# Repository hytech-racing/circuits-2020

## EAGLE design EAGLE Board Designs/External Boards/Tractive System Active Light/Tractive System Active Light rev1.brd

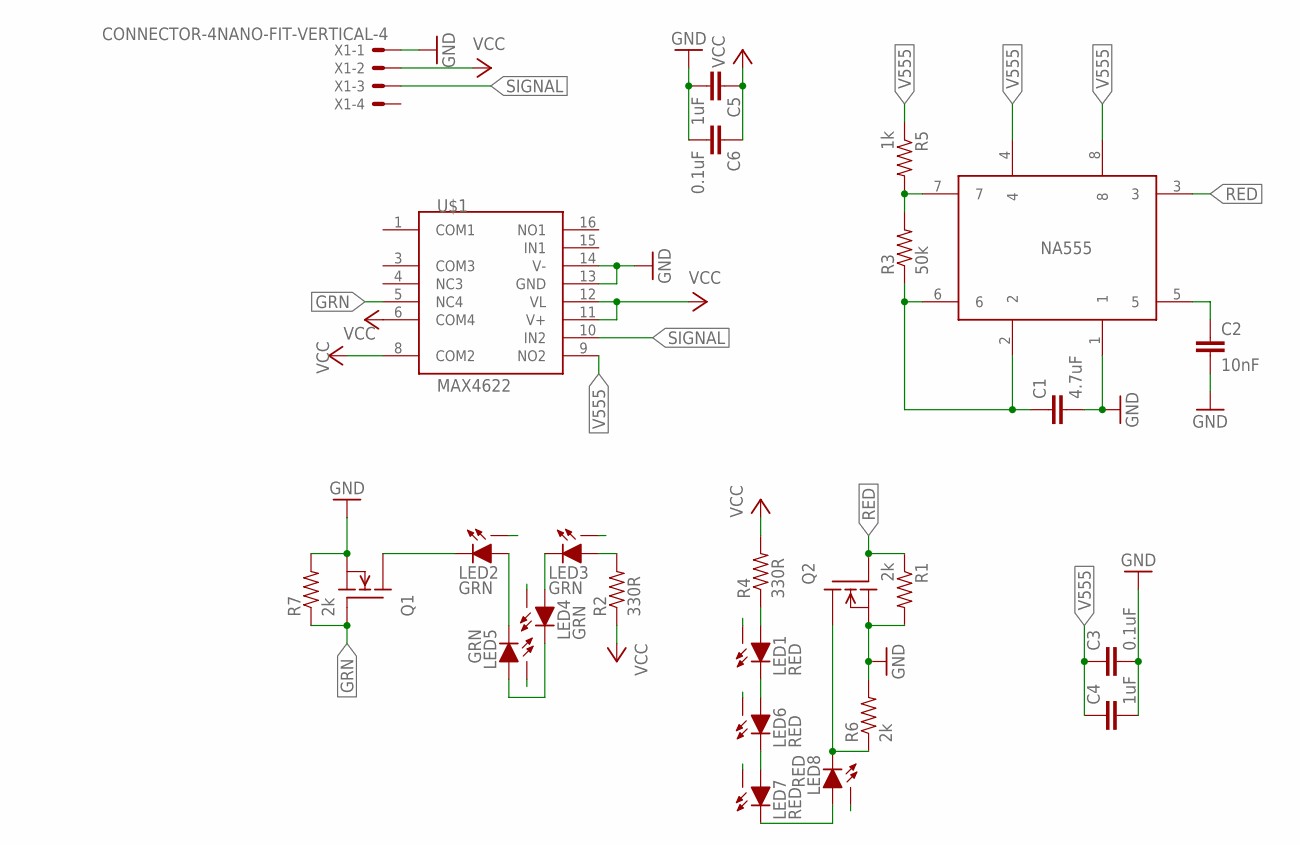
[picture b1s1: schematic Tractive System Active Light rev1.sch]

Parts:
C1: 4.7uF; 0603-CAP
C2: 10nF; 0603-CAP
C3, C6: 0.1uF; 0603-CAP
C4, C5: 1uF; 0603-CAP
LED1, LED6, LED7, LED8: RED; XP-E2
LED2, LED3, LED4, LED5: GRN; XP-E2
NA555: NA555SO-8; SOIC-08
Q1, Q2: DMG3406LSOT; SOT23
R1, R6, R7: 2k; 0603-RES
R2, R4: 330R; 0603-RES
R3: 50k; 0603-RES
R5: 1k; 0603-RES
U$1: MAX4622; SO16
X1: CONNECTOR-4NANO-FIT-VERTICAL-4; NANO-FIT_VERTICAL-4

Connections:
GND: C1.2, C2.2, C3.2, C4.2, C5.2, C6.2, NA555.1, Q1.2 (S), Q2.2 (S), R1.2, R6.2, R7.2, U$1.13 (GND), U$1.14 (V-), X1.P$1
GRN: Q1.1 (G), R7.1, U$1.5 (NC4)
LED1_THERM: LED1.X
LED2_THERM: LED2.X
LED3_THERM: LED3.X
LED4_THERM: LED4.X
LED5_THERM: LED5.X
LED6_THERM: LED6.X
LED7_THERM: LED7.X
LED8_THERM: LED8.X
unnamed: LED4.C, LED5.A
unnamed: LED2.C, Q1.3 (D)
unnamed: LED3.C, LED4.A
unnamed: LED3.A, R2.2
unnamed: C1.1, NA555.2, NA555.6, R3.1
unnamed: NA555.7, R3.2, R5.2
unnamed: LED8.C, Q2.3 (D), R6.1
unnamed: LED1.A, R4.1
unnamed: C2.1, NA555.5
unnamed: LED2.A, LED5.C
unnamed: LED1.C, LED6.A
unnamed: LED6.C, LED7.A
unnamed: LED7.C, LED8.A
RED: NA555.3, Q2.1 (G), R1.1
SIGNAL: U$1.10 (IN2), X1.P$3
V555: C3.1, C4.1, NA555.4, NA555.8, R5.1, U$1.9 (NO2)
VCC: C5.1, C6.1, R2.1, R4.2, U$1.6 (COM4), U$1.8 (COM2), U$1.11 (V+), U$1.12 (VL), X1.P$2

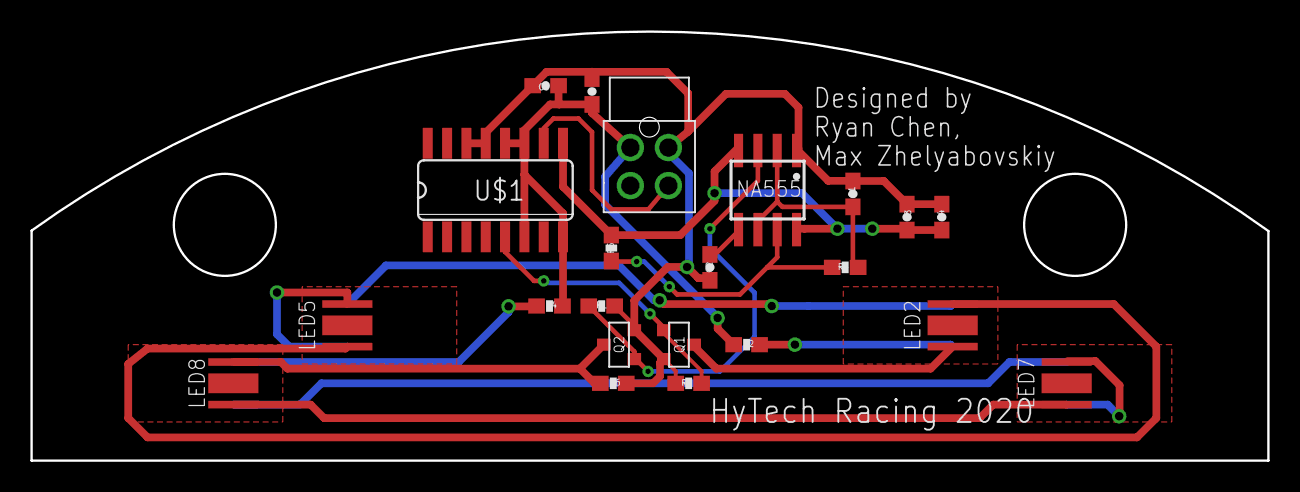
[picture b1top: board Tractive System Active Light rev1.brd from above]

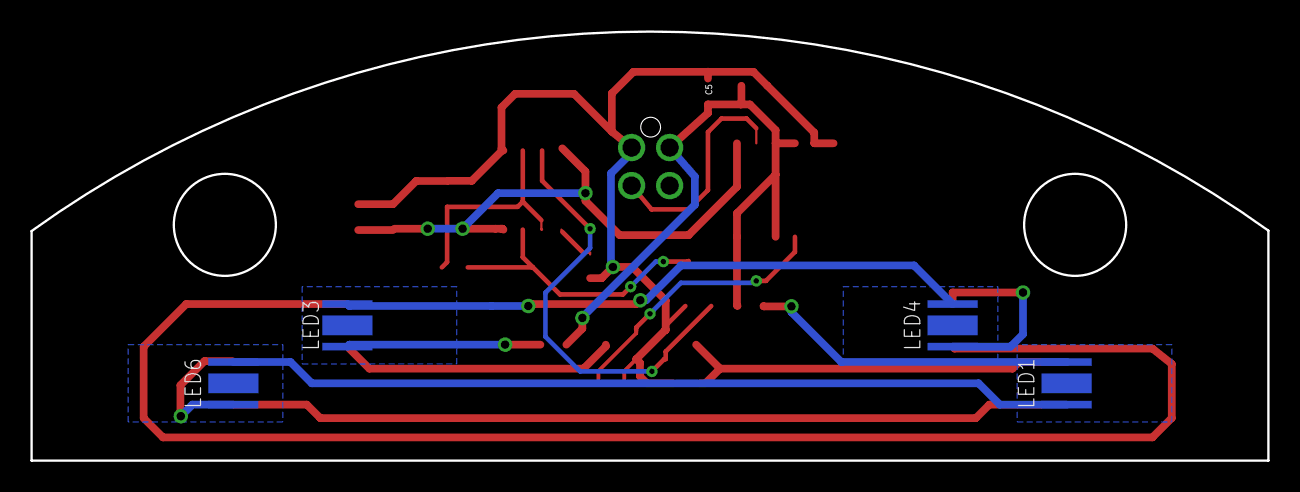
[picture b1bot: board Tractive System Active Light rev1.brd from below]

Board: 2 copper layers, 81.3 x 28.2 mm, 26 parts (4 on the bottom side), 19 nets.

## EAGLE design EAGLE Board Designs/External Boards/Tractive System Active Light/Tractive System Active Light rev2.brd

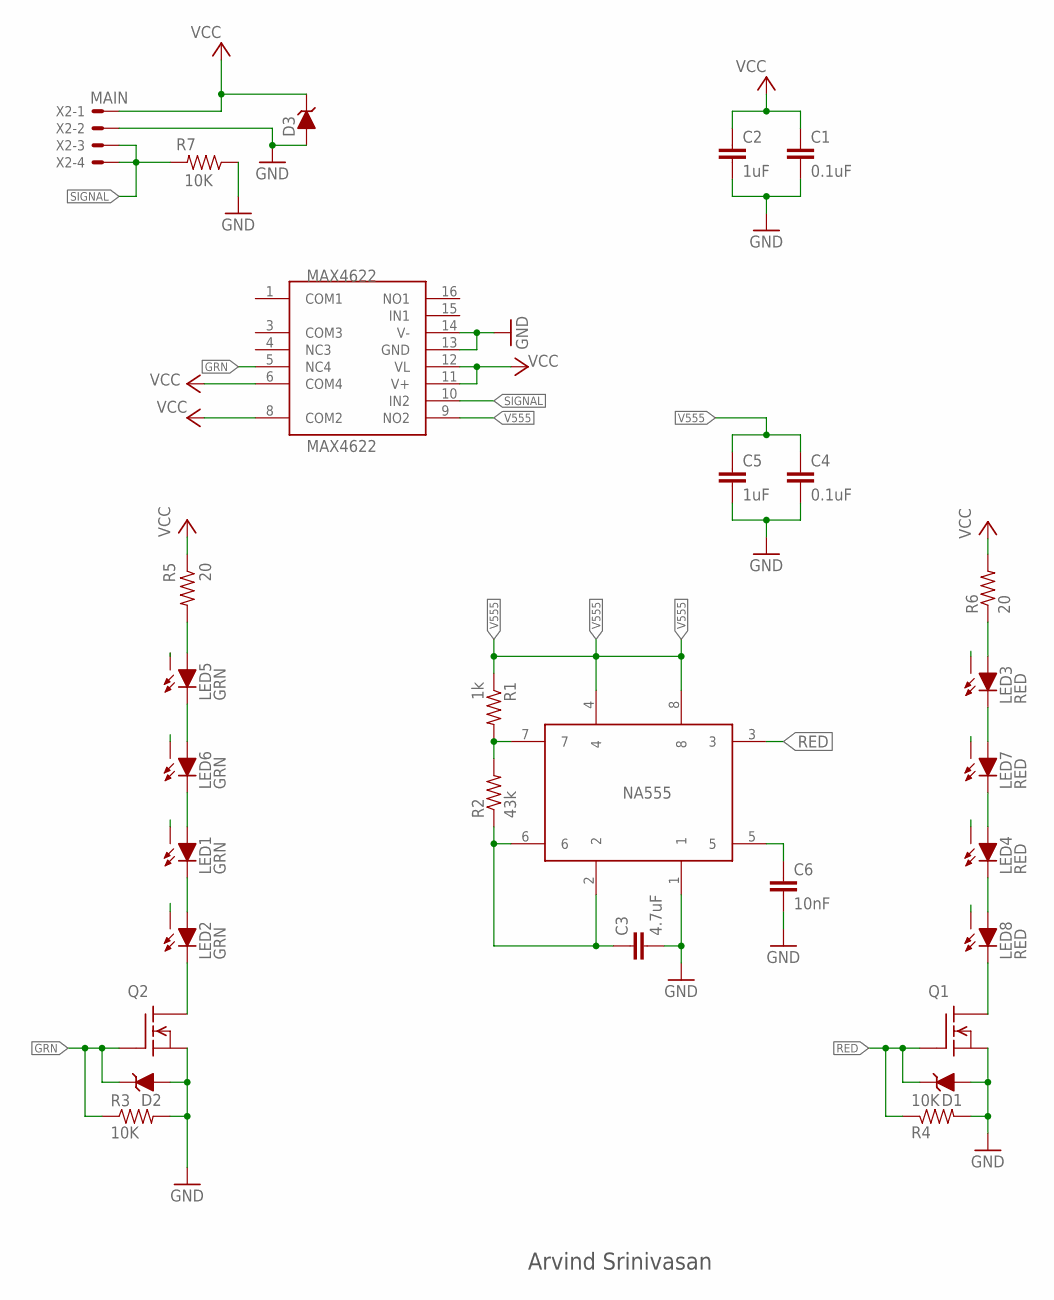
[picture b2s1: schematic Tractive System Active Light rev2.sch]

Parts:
C1, C4: 0.1uF; 0603-CAP; TOLERANCE 5%; VOLTAGE 25V
C2, C5: 1uF; 0603-CAP; TOLERANCE 5%; VOLTAGE 25V
C3: 4.7uF; 0603-CAP; TOLERANCE 5%; VOLTAGE 25V
C6: 10nF; 0603-CAP; TOLERANCE 5%; VOLTAGE 25V
D1, D2: DIODE_ZENER; SOT23
D3: DIODE_ZENER0603; 0603_D
LED1, LED2, LED5, LED6: GRN; XP-E2
LED3, LED4, LED7, LED8: RED; XP-E2
MAX4622: MAX4622; SO16
NA555: NA555SO-8; SOIC-08
Q1, Q2: DMG3406LSOT; SOT23
R1: 1k; 0603-RES; TOLERANCE 1%
R2: 43k; 0603-RES; TOLERANCE 1%
R3, R4, R7: 10K; 0603-RES; TOLERANCE 1%
R5, R6: 20; 0603-RES; TOLERANCE 1%
X2: MAIN; NANO-FIT_RIGHT_ANGLE-4-SURFACE

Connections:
GND: C1.2, C2.2, C3.2, C4.2, C5.2, C6.2, D1.1 (A), D2.1 (A), D3.A, MAX4622.13 (GND), MAX4622.14 (V-), NA555.1, Q1.2 (S), Q2.2 (S), R3.2, R4.2, R7.1, X2.2
GRN: D2.3 (C), MAX4622.5 (NC4), Q2.1 (G), R3.1
unnamed: LED1.A, LED6.C
unnamed: LED2.C, Q2.3 (D)
unnamed: LED5.C, LED6.A
unnamed: LED5.A, R5.2
unnamed: C3.1, NA555.2, NA555.6, R2.1
unnamed: NA555.7, R1.2, R2.2
unnamed: LED8.C, Q1.3 (D)
unnamed: LED3.A, R6.1
unnamed: C6.1, NA555.5
unnamed: LED1.C, LED2.A
unnamed: LED3.C, LED7.A
unnamed: LED4.A, LED7.C
unnamed: LED4.C, LED8.A
RED: D1.3 (C), NA555.3, Q1.1 (G), R4.1
SIGNAL: MAX4622.10 (IN2), R7.2, X2.3, X2.4
THERM: LED1.X, LED2.X, LED3.X, LED4.X, LED5.X, LED6.X, LED7.X, LED8.X
V555: C4.1, C5.1, MAX4622.9 (NO2), NA555.4, NA555.8, R1.1
VCC: C1.1, C2.1, D3.C, MAX4622.6 (COM4), MAX4622.8 (COM2), MAX4622.11 (V+), MAX4622.12 (VL), R5.1, R6.2, X2.1

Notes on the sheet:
Arvind Srinivasan

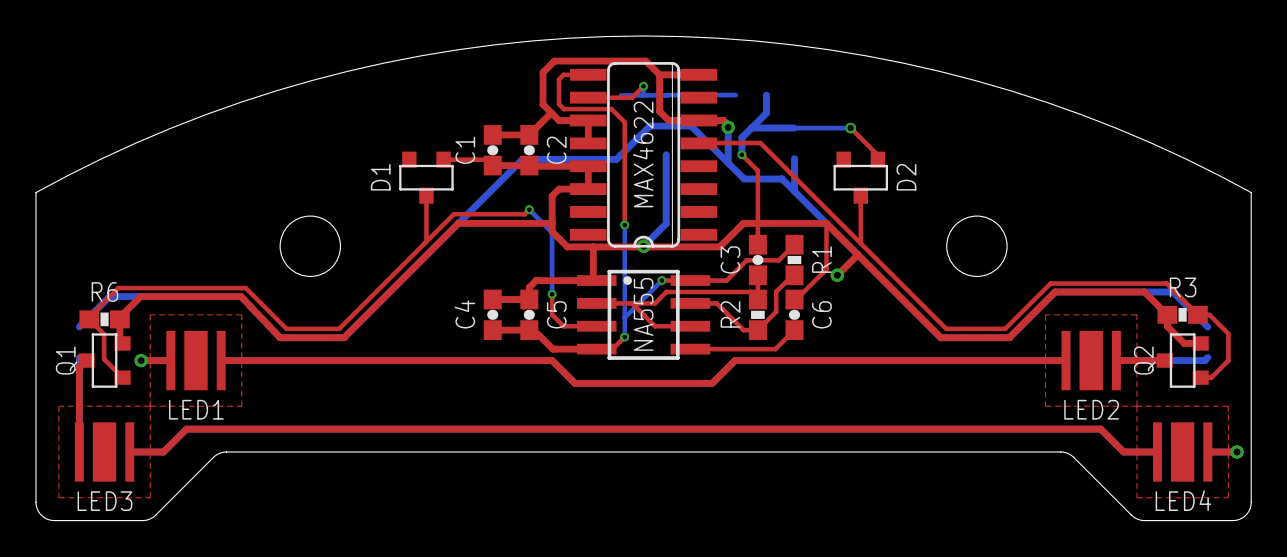
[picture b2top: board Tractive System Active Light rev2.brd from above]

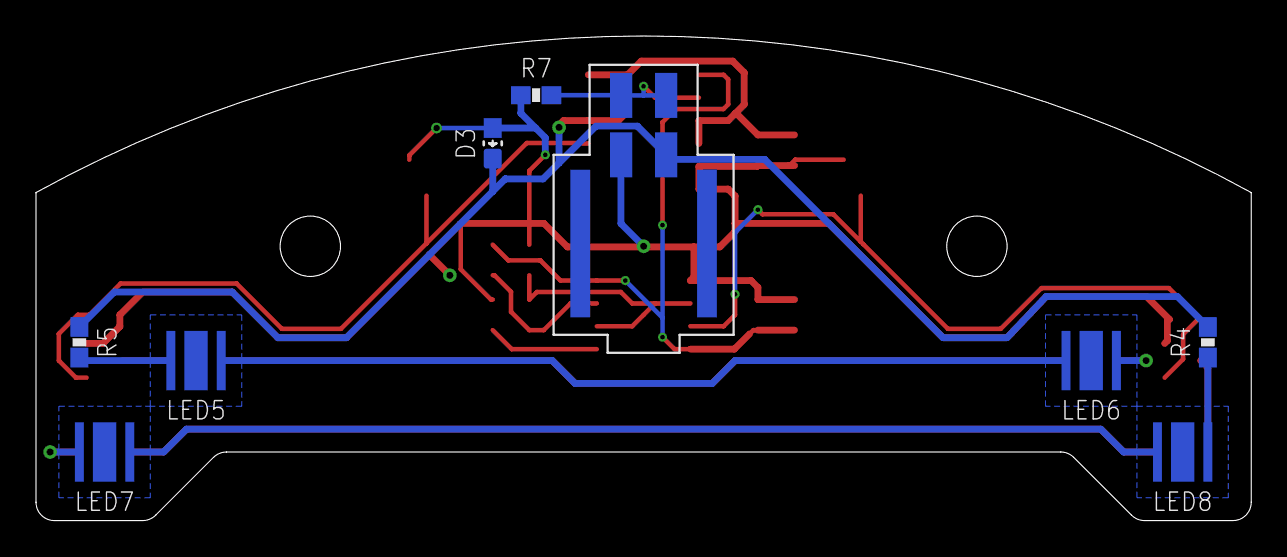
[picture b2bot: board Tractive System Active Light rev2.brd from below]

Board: 2 copper layers, 67.5 x 26.9 mm, 31 parts (9 on the bottom side), 20 nets.

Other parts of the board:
$$U$1: M3_MOUNTING
U$2: M3_MOUNTING

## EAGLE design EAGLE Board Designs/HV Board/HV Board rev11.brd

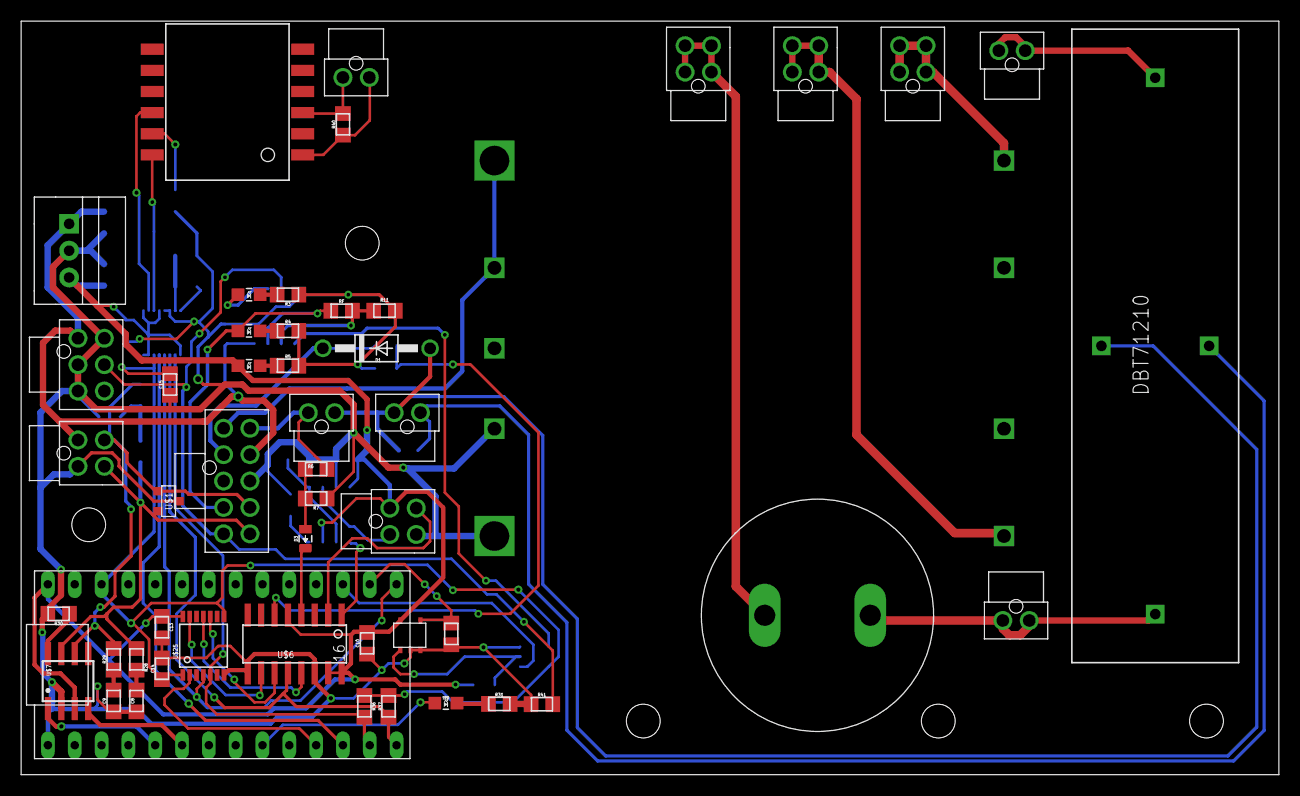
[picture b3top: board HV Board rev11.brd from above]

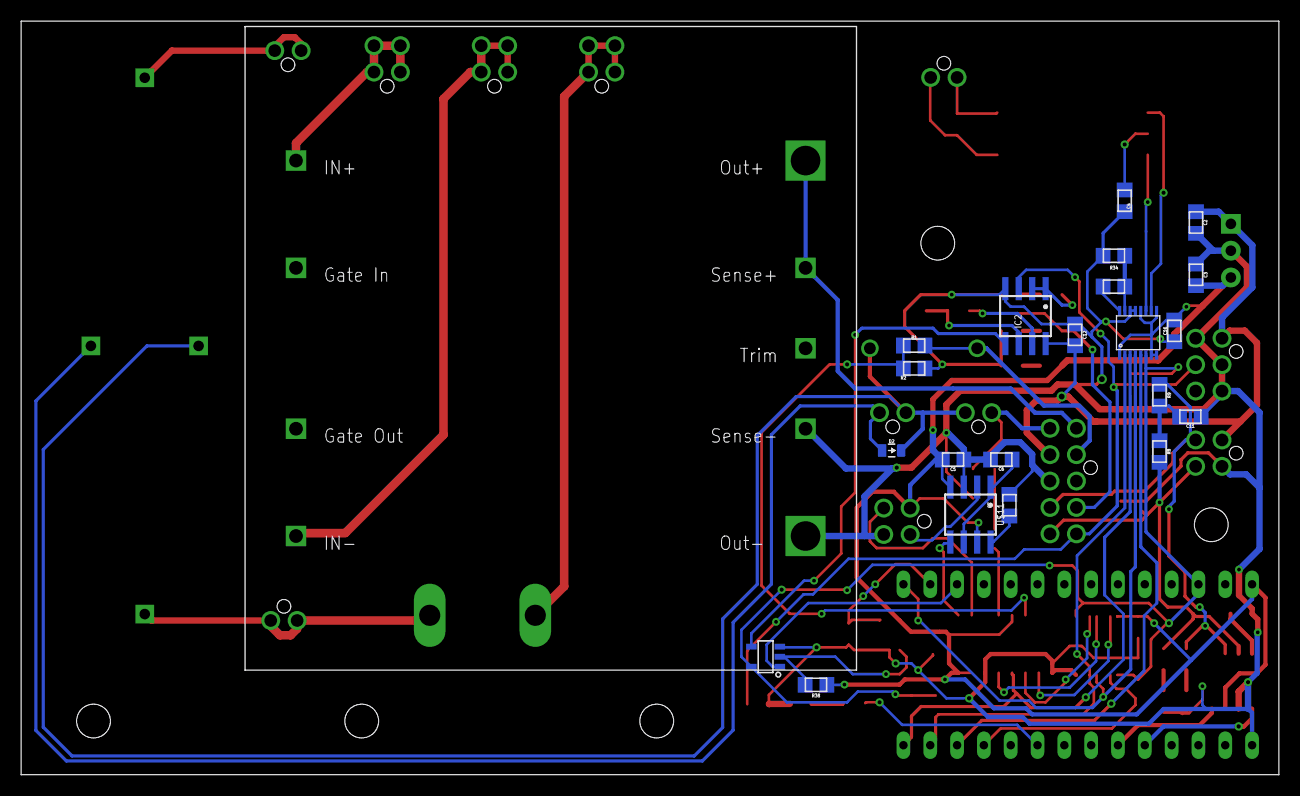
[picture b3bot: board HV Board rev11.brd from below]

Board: 2 copper layers, 119.1 x 71.4 mm, 72 parts (22 on the bottom side), 58 nets.

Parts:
BMS-OK: GREEN; LED-805
C1: 180µF; LLS2V221MELZ
C2, C3: 10uF; 0805
C4: 27pF; 0805
C5, C6, C10, C12, C13, C14, C15, C16: 0.1uF; 0805
C7: 530pF; 0805
C8, C9: 560pF; 0805
C11: 4.7nF; 0805
CURRENT: CURRENT; NANO-FIT_VERTICAL-4
D1: DIODE; DO-41
D2, D3: TS4148 RYG; 0805_D
DISCH+: DISCHARGE+; NANO-FIT_VERTICAL-2
HV+FUSED_1A-IMD+: HV+; NANO-FIT_VERTICAL-4
HV+UNFUSED: HV+UNFUSED; NANO-FIT_VERTICAL-2
HV-FUSED_1A-IMD-: HV-; NANO-FIT_VERTICAL-4
HV-UNFUSED_DISCHARGE-: HV-UNFUSED; NANO-FIT_VERTICAL-4
IC1: OKI-78SR-5; OKI-78SR
IC2: NE5532SOIC; SOIC-08
IMD: CONNECTOR-6NANO-FIT_VERTICAL-6; NANO-FIT_VERTICAL-6
IMD-OK: YELLOW; LED-805
INTERLOCK: INTERLOCK; NANO-FIT_VERTICAL-2
ISO_SPI: ISO_SPI; NANO-FIT_VERTICAL-2
LED: BLUE; LED-805
MAIN: MAIN; NANO-FIT_VERTICAL-10
ON-LED: PURPLE; LED-805
POWER: POWER; NANO-FIT_VERTICAL-4
R1, R6: 43k; 0805
R2, R7: 12k; 0805
R3: 820; 0805
R4, R36, R37, R41: 2k; 0805
R5: 270; 0805
R8, R9: 60; 0805
R11, R30, R33, R34: 1k; 0805
R28, R29, R40: 100; 0805
R31: 43; 0805
R38: 430; 0805
R42: 10k; 0805
RELAYS: RELAYS; NANO-FIT_VERTICAL-2
RF: 2k; 0805
U$1: CDSOT23-T24CAN-Q; SOT23
U$2: HM2102NLT
U$3: SN74LVC1G08; SOT-23-5
U$4: DBT71210
U$5: HV_DCDC_VI-J71-CZ
U$6: MCP3208SOIC; SOIC-16
U$7: MCP2551; SOIC-08
U$8: LTC6820; MSOP-16
U$9: TEENSY_3.2_SIMPLE
U$10: STWD100; SOT23-5
U$11: MAX7480; SOIC-08
U$25: TXB0104TSSOP; TSSOP-14

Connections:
+3V3: C14.1, C15.2, R36.1, R37.1, U$3.5, U$8.6, U$9.3.3V, U$25.1, U$25.8
+5V: C3.1, C5.1, C10.1, C13.1, C16.2, CURRENT.P$1, IC1.3, ON-LED.A, R38.1, U$6.5, U$6.15, U$6.16, U$7.3, U$8.1, U$8.7, U$8.8, U$8.9, U$8.12, U$9.VIN, U$10.VCC, U$11.4, U$11.7, U$25.14
+12V: C2.1, C12.1, IC1.1, IC2.8, IMD.P$1, MAIN.P$7, POWER.P$1
BMS_OK_3.3V: IC2.5, U$3.4
BMS_OK_10V: BMS-OK.A, IC2.7, MAIN.P$4, RF.2
CANH: MAIN.P$10, POWER.P$4, R8.2, R28.2, U$1.2, U$7.7
CANL: MAIN.P$9, POWER.P$3, R9.2, R29.2, U$1.1, U$7.6
CHARGE_ENABLE: D1.C, MAIN.P$2, R1.1
CS_LTC6820: U$8.5, U$9.D10(TX2)
CS_MCP3208_3.3V: U$9.D9(RX2), U$25.2
CUR_SENSE: CURRENT.P$2, U$11.2
DISCHARGE_RELAY_GND: D2.A, RELAYS.P$2, U$4.COIL-
GND: C2.2, C3.2, C4.2, C5.2, C6.2, C7.2, C8.1, C9.1, C10.2, C11.1, C12.2, C13.2, C14.2, C15.1, C16.1, CURRENT.P$4, IC1.2, IC2.4, IMD.P$2, IMD.P$3, IMD.P$4, MAIN.P$8, POWER.P$2, R2.1, R3.1, R4.2, R5.2, R7.1, R11.1, R30.1, R31.2, R34.2, R41.2, R42.2, U$1.3, U$3.3, U$5.8SENSE-, U$5.9VOUT-, U$6.9, U$6.14, U$7.2, U$8.13, U$8.14, U$9.GND, U$10.EN, U$10.GND, U$11.3, U$25.7
HV+FUSED_1A: HV+FUSED_1A-IMD+.P$1, HV+FUSED_1A-IMD+.P$2, HV+FUSED_1A-IMD+.P$3, HV+FUSED_1A-IMD+.P$4, U$5.1VIN+
HV+UNFUSED: C1.P$1, HV+UNFUSED.P$1, HV+UNFUSED.P$2, U$4.CONTACT1
HV+UNFUSED_FSAE_DISCHARGE: DISCH+.P$1, DISCH+.P$2, U$4.CONTACT2
HV-FUSED_1A: HV-FUSED_1A-IMD-.P$1, HV-FUSED_1A-IMD-.P$2, HV-FUSED_1A-IMD-.P$3, HV-FUSED_1A-IMD-.P$4, U$5.4VIN-
HV-UNFUSED: C1.P$2, HV-UNFUSED_DISCHARGE-.P$1, HV-UNFUSED_DISCHARGE-.P$2, HV-UNFUSED_DISCHARGE-.P$3, HV-UNFUSED_DISCHARGE-.P$4
IM: U$2.P$10, U$8.10
IP: U$2.P$12, U$8.11
ISOSPI-M: ISO_SPI.P$2, R40.2, U$2.P$3
ISOSPI-P: ISO_SPI.P$1, R40.1, U$2.P$1
MISO: R37.2, U$6.12, U$8.3, U$9.D12
MOSI_5V: U$6.11, U$25.10
MOSI_TEENSY: R36.2, U$8.2, U$9.D11, U$25.5
unnamed: U$6.1, U$11.5
unnamed: C6.1, U$11.1, U$11.6
unnamed: ON-LED.C, R5.1
unnamed: C7.1, U$11.8
unnamed: U$6.10, U$25.13
unnamed: D3.A, R6.2, R7.2
unnamed: D3.C, U$6.4
unnamed: C11.2, R8.1, R9.1
unnamed: IC2.6, R11.2, RF.1
unnamed: R1.2, R2.2, U$6.6
unnamed: U$7.1, U$9.D3(CANTX)
unnamed: R30.2, U$7.8
unnamed: C8.2, R28.1
unnamed: C9.2, R29.1
unnamed: LED.C, R31.1
unnamed: R33.1, U$8.16
unnamed: R33.2, R34.1, U$8.15
unnamed: C4.1, U$2.P$11
unnamed: U$7.4, U$9.D4(CANRX)
unnamed: LED.A, U$9.D7(RX3)
unnamed: R38.2, U$3.2, U$10.WDO
unnamed: U$3.1, U$9.A1
unnamed: IC2.1, IC2.2, IMD-OK.A
unnamed: BMS-OK.C, R4.1
unnamed: IMD-OK.C, R3.2
unnamed: R42.1, U$9.A0, U$10.WDI
OKHS: IC2.3, IMD.P$5, MAIN.P$5, R41.1
SCK_5V: U$6.13, U$25.11
SCK_TEENSY: U$8.4, U$9.D13, U$25.4
SHUTDOWN_G: INTERLOCK.P$1, MAIN.P$6, R6.1
SHUTDOWN_H: D1.A, D2.C, INTERLOCK.P$2, RELAYS.P$1, U$4.COIL+
TEMP_SENSE: CURRENT.P$3, U$6.2
TSAL+: MAIN.P$1, U$5.5VOUT+, U$5.6SENSE+

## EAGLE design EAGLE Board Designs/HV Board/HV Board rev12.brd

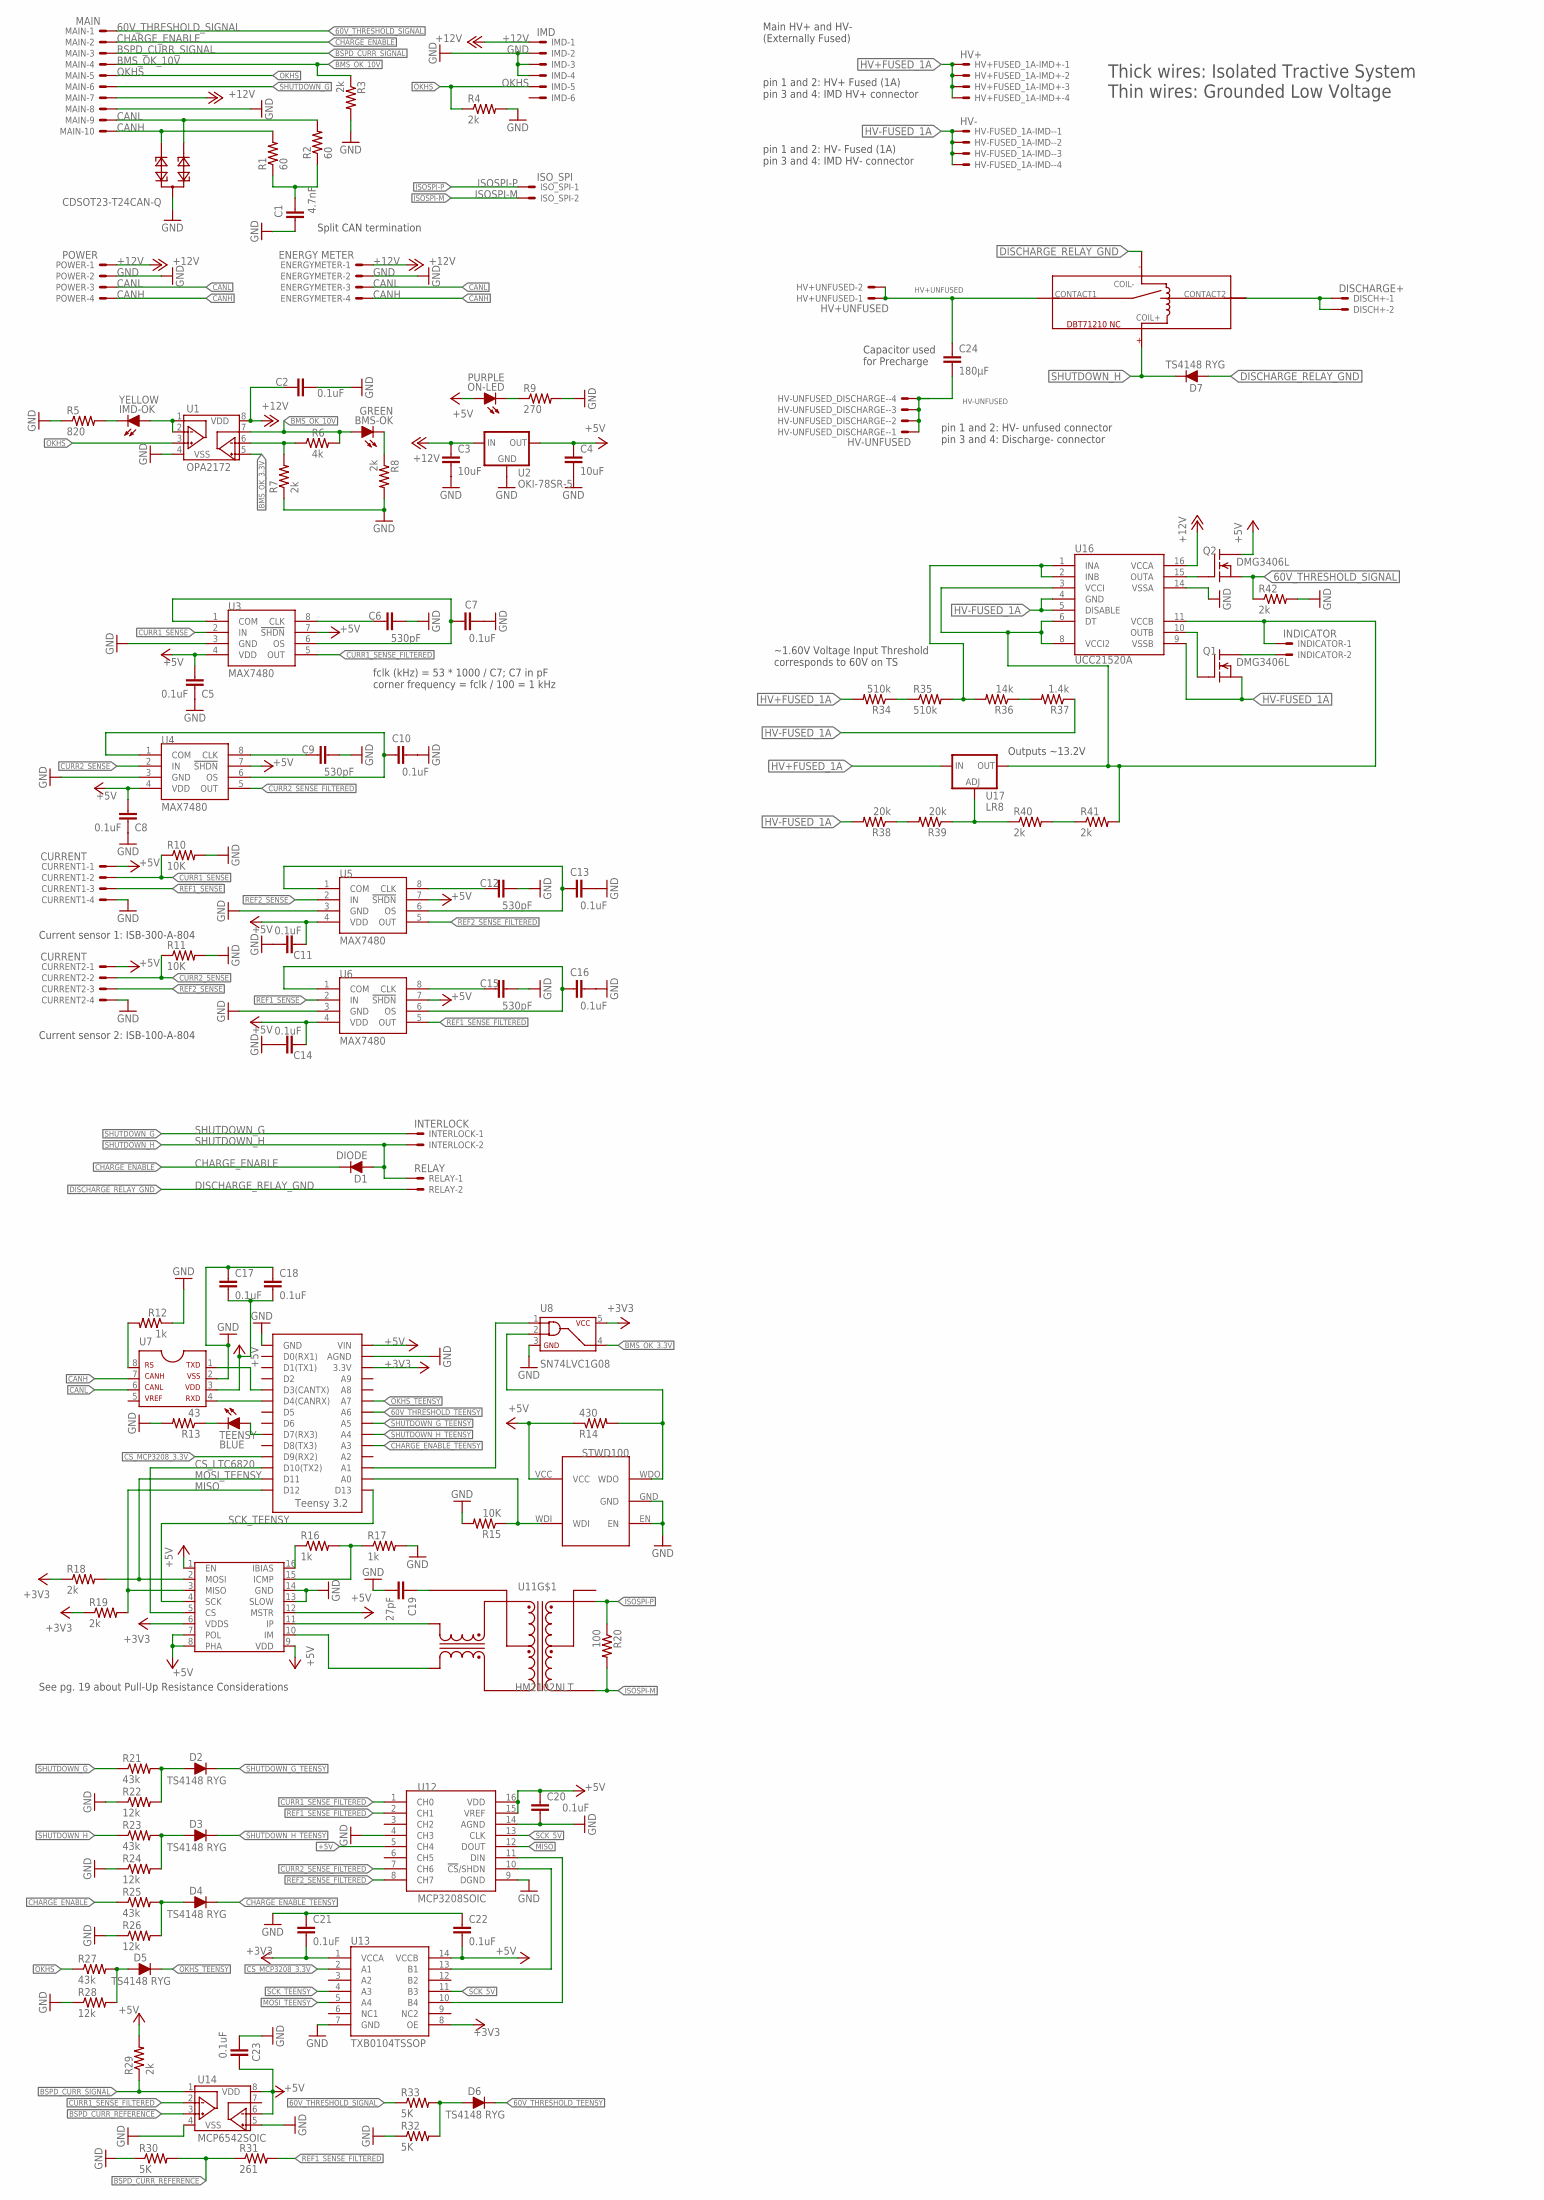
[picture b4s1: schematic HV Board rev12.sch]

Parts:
BMS-OK: GREEN; LED-805
C1: 4.7nF; 0603-CAP; TOLERANCE 5%; VOLTAGE 50V
C2, C5, C7, C8, C10, C11, C13, C14, C16, C17, C18, C20, C21, C22, C23: 0.1uF; 0603-CAP; TOLERANCE 5%; VOLTAGE 10V
C3, C4: 10uF; 0603-CAP; TOLERANCE 5%; VOLTAGE 25V
C6, C9, C12, C15: 530pF; 0603-CAP; TOLERANCE 1%; VOLTAGE 10V
C19: 27pF; 0603-CAP; TOLERANCE 5%; VOLTAGE 10V
C24: 180µF; LLS2V221MELZ; TOLERANCE 20%; VOLTAGE 350V
CURRENT1, CURRENT2: CURRENT; NANO-FIT_VERTICAL-4
D1: DIODE; DO-41
D2, D3, D4, D5, D6, D7: TS4148 RYG; 0805_D
DISCH+: DISCHARGE+; NANO-FIT_VERTICAL-2
ENERGYMETER: ENERGY METER; NANO-FIT_VERTICAL-4
HV+FUSED_1A-IMD+: HV+; NANO-FIT_VERTICAL-4
HV+UNFUSED: HV+UNFUSED; NANO-FIT_VERTICAL-2
HV-FUSED_1A-IMD-: HV-; NANO-FIT_VERTICAL-4
HV-UNFUSED_DISCHARGE-: HV-UNFUSED; NANO-FIT_VERTICAL-4
IMD: IMD; NANO-FIT_VERTICAL-6
IMD-OK: YELLOW; LED-805
INDICATOR: INDICATOR; NANO-FIT_VERTICAL-2
INTERLOCK: INTERLOCK; NANO-FIT_VERTICAL-2
ISO_SPI: ISO_SPI; NANO-FIT_VERTICAL-2
MAIN: MAIN; NANO-FIT_VERTICAL-10
ON-LED: PURPLE; LED-805
POWER: POWER; NANO-FIT_VERTICAL-4
Q1, Q2: DMG3406L; SOT23
R1, R2: 60; 0603-RES; TOLERANCE 1%
R3, R4, R7, R8, R18, R19, R29, R42: 2k; 0603-RES; TOLERANCE 1%
R5: 820; 0603-RES; TOLERANCE 1%
R6: 4k; 0603-RES; TOLERANCE 1%
R9: 270; 0603-RES; TOLERANCE 1%
R10, R11, R15: 10K; 0603-RES; TOLERANCE 1%
R12, R16, R17: 1k; 0603-RES; TOLERANCE 1%
R13: 43; 0603-RES; TOLERANCE 1%
R14: 430; 0603-RES; TOLERANCE 1%
R20: 100; 0603-RES; TOLERANCE 1%
R21, R23, R25, R27: 43k; 0603-RES; TOLERANCE 1%
R22, R24, R26, R28: 12k; 0603-RES; TOLERANCE 1%
R30, R32, R33: 5K; 0603-RES; TOLERANCE 1%
R31: 261; 0603-RES; TOLERANCE 1%
R34, R35: 510k; 0805; TOLERANCE 1%
R36: 14k; 0805; TOLERANCE 1%
R37: 1.4k; 0805; TOLERANCE 1%
R38, R39: 20k; 0805; TOLERANCE 1%
R40, R41: 2k; 0805; TOLERANCE 1%
RELAY: RELAY; NANO-FIT_VERTICAL-2
TEENSY: BLUE; LED-805
TEENSY3.2: TEENSY_3.2_SIMPLE
U1: OPA2172; SOIC-08
U2: OKI-78SR-5; OKI-78SR
U3, U4, U5, U6: MAX7480; SOIC-08
U7: MCP2551; SOIC-08
U8: SN74LVC1G08; SOT-23-5
U9: LTC6820; MSOP-16
U10: STWD100NYWY3F; SOT23-5
U11: HM2102NLT
U12: MCP3208SOIC; SOIC-16
U13: TXB0104TSSOP; TSSOP-14
U14: MCP6542SOIC; SOIC-08
U15: DBT71210
U16: UCC21520A; SO16-DW
U17: LR8; TO-252
U18: CDSOT23-T24CAN-Q; SOT23

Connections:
60V_THRESHOLD_SIGNAL: MAIN.P$1, Q2.2 (S), R33.1, R42.1
60V_THRESHOLD_TEENSY: D6.C, TEENSY3.2.A6
+3V3: C21.1, R18.1, R19.1, TEENSY3.2.3.3V, U8.5, U9.6 (VDDS), U13.1 (VCCA), U13.8 (OE)
+5V: C4.1, C5.1, C8.1, C11.1, C14.1, C17.1, C18.1, C20.1, C22.1, C23.1, CURRENT1.P$1, CURRENT2.P$1, ON-LED.A, Q2.3 (D), R14.1, R29.2, TEENSY3.2.VIN, U2.3 (OUT), U3.4 (VDD), U3.7 (!SHDN), U4.4 (VDD), U4.7 (!SHDN), U5.4 (VDD), U5.7 (!SHDN), U6.4 (VDD), U6.7 (!SHDN), U7.3, U9.1 (EN), U9.7 (POL), U9.8 (PHA), U9.9 (VDD), U9.12 (MSTR), U10.VCC, U12.5 (CH4), U12.15 (VREF), U12.16 (VDD), U13.14 (VCCB), U14.6 (VINB-), U14.8 (VDD)
+12V: C2.1, C3.1, ENERGYMETER.P$1, IMD.P$1, MAIN.P$7, POWER.P$1, U1.8 (VDD), U2.1 (IN), U16.16 (VCCA)
BMS_OK_3.3V: U1.5 (VINB+), U8.4
BMS_OK_10V: BMS-OK.A, MAIN.P$4, R3.1, R6.2, U1.7 (VOUTB)
BSPD_CURR_REFERENCE: R30.2, R31.1, U14.3 (VINA+)
BSPD_CURR_SIGNAL: MAIN.P$3, R29.1, U14.1 (VOUTA)
CANH: ENERGYMETER.P$4, MAIN.P$10, POWER.P$4, R1.2, U7.7, U18.2
CANL: ENERGYMETER.P$3, MAIN.P$9, POWER.P$3, R2.2, U7.6, U18.1
CHARGE_ENABLE: D1.C, MAIN.P$2, R25.1
CHARGE_ENABLE_TEENSY: D4.C, TEENSY3.2.A3
CS_LTC6820: TEENSY3.2.D10(TX2), U9.5 (CS)
CS_MCP3208_3.3V: TEENSY3.2.D9(RX2), U13.2 (A1)
CURR1_SENSE: CURRENT1.P$2, R10.1, U3.2 (IN)
CURR1_SENSE_FILTERED: U3.5 (OUT), U12.1 (CH0), U14.2 (VINA-)
CURR2_SENSE: CURRENT2.P$2, R11.1, U4.2 (IN)
CURR2_SENSE_FILTERED: U4.5 (OUT), U12.7 (CH6)
DISCHARGE_RELAY_GND: D7.A, RELAY.P$2, U15.COIL-
GND: C1.1, C2.2, C3.2, C4.2, C5.2, C6.2, C7.2, C8.2, C9.2, C10.2, C11.2, C12.2, C13.2, C14.2, C15.2, C16.2, C17.2, C18.2, C19.2, C20.2, C21.2, C22.2, C23.2, CURRENT1.P$4, CURRENT2.P$4, ENERGYMETER.P$2, IMD.P$2, IMD.P$3, IMD.P$4, MAIN.P$8, POWER.P$2, R3.2, R4.2, R5.1, R7.1, R8.2, R9.2, R10.2, R11.2, R12.1, R13.2, R15.2, R17.2, R22.1, R24.1, R26.1, R28.1, R30.1, R32.1, R42.2, TEENSY3.2.AGND, TEENSY3.2.GND, U1.4 (VSS), U2.2 (GND), U3.3 (GND), U4.3 (GND), U5.3 (GND), U6.3 (GND), U7.2, U8.3, U9.13 (SLOW), U9.14 (GND), U10.EN, U10.GND, U12.4 (CH3), U12.9 (DGND), U12.14 (AGND), U13.7 (GND), U14.4 (VSS), U14.5 (VINB+), U16.14 (VSSA), U18.3
HV+FUSED_1A: HV+FUSED_1A-IMD+.P$1, HV+FUSED_1A-IMD+.P$2, HV+FUSED_1A-IMD+.P$3, HV+FUSED_1A-IMD+.P$4, R34.2, U17.1 (IN)
HV+UNFUSED: C24.P$1 (1), HV+UNFUSED.P$1, HV+UNFUSED.P$2, U15.CONTACT1
HV+UNFUSED_FSAE_DISCHARGE: DISCH+.P$1, DISCH+.P$2, U15.CONTACT2
HV-FUSED_1A: HV-FUSED_1A-IMD-.P$1, HV-FUSED_1A-IMD-.P$2, HV-FUSED_1A-IMD-.P$3, HV-FUSED_1A-IMD-.P$4, Q1.2 (S), R37.1, R38.2, U16.4 (GND), U16.5 (DISABLE), U16.9 (VSSB)
HV-UNFUSED: C24.P$2 (2), HV-UNFUSED_DISCHARGE-.P$1, HV-UNFUSED_DISCHARGE-.P$2, HV-UNFUSED_DISCHARGE-.P$3, HV-UNFUSED_DISCHARGE-.P$4
IM: U9.10 (IM), U11.P$10 (TD-)
IP: U9.11 (IP), U11.P$12 (TD+)
ISOSPI-M: ISO_SPI.P$2, R20.2, U11.P$3 (MX-)
ISOSPI-P: ISO_SPI.P$1, R20.1, U11.P$1 (MX+)
MISO: R19.2, TEENSY3.2.D12, U9.3 (MISO), U12.12 (DOUT)
MOSI_5V: U12.11 (DIN), U13.10 (B4)
MOSI_TEENSY: R18.2, TEENSY3.2.D11, U9.2 (MOSI), U13.5 (A4)
unnamed: INDICATOR.P$2, Q1.3 (D)
unnamed: C7.1, U3.1 (COM), U3.6 (OS)
unnamed: ON-LED.C, R9.1
unnamed: C6.1, U3.8 (CLK)
unnamed: U12.10 (!CS!/SHDN), U13.13 (B1)
unnamed: D2.A, R21.2, R22.2
unnamed: D4.A, R25.2, R26.2
unnamed: D6.A, R32.2, R33.2
unnamed: C1.2, R1.1, R2.1
unnamed: R6.1, R7.2, U1.6 (VINB-)
unnamed: D3.A, R23.2, R24.2
unnamed: R34.1, R35.1
unnamed: R39.1, R40.1, U17.3 (ADJ)
unnamed: R35.2, R36.2, U16.1 (INA), U16.2 (INB)
unnamed: R36.1, R37.2
unnamed: Q2.1 (G), U16.15 (OUTA)
unnamed: D5.A, R27.2, R28.2
unnamed: Q1.1 (G), U16.10 (OUTB)
unnamed: INDICATOR.P$1, R41.2, U16.3 (VCCI), U16.6 (DT), U16.8 (VCCI2), U16.11 (VCCB), U17.2(TAB) (OUT)
unnamed: TEENSY3.2.D3(CANTX), U7.1
unnamed: R12.2, U7.8
unnamed: R13.1, TEENSY.C
unnamed: R16.1, U9.16 (IBIAS)
unnamed: R16.2, R17.1, U9.15 (ICMP)
unnamed: C19.1, U11.P$11 (TCT)
unnamed: TEENSY3.2.D4(CANRX), U7.4
unnamed: TEENSY.A, TEENSY3.2.D7(RX3)
unnamed: R14.2, U8.2, U10.WDO
unnamed: TEENSY3.2.A1, U8.1
unnamed: IMD-OK.A, U1.1 (VOUTA), U1.2 (VINA-)
unnamed: R40.2, R41.1
unnamed: BMS-OK.C, R8.1
unnamed: IMD-OK.C, R5.2
unnamed: R38.1, R39.2
unnamed: C16.1, U6.1 (COM), U6.6 (OS)
unnamed: C15.1, U6.8 (CLK)
unnamed: R15.1, TEENSY3.2.A0, U10.WDI
unnamed: C10.1, U4.1 (COM), U4.6 (OS)
unnamed: C9.1, U4.8 (CLK)
unnamed: C13.1, U5.1 (COM), U5.6 (OS)
unnamed: C12.1, U5.8 (CLK)
OKHS: IMD.P$5, MAIN.P$5, R4.1, R27.1, U1.3 (VINA+)
OKHS_TEENSY: D5.C, TEENSY3.2.A7
REF1_SENSE: CURRENT1.P$3, U6.2 (IN)
REF1_SENSE_FILTERED: R31.2, U6.5 (OUT), U12.2 (CH1)
REF2_SENSE: CURRENT2.P$3, U5.2 (IN)
REF2_SENSE_FILTERED: U5.5 (OUT), U12.8 (CH7)
SCK_5V: U12.13 (CLK), U13.11 (B3)
SCK_TEENSY: TEENSY3.2.D13, U9.4 (SCK), U13.4 (A3)
SHUTDOWN_G: INTERLOCK.P$1, MAIN.P$6, R21.1
SHUTDOWN_G_TEENSY: D2.C, TEENSY3.2.A5
SHUTDOWN_H: D1.A, D7.C, INTERLOCK.P$2, R23.1, RELAY.P$1, U15.COIL+
SHUTDOWN_H_TEENSY: D3.C, TEENSY3.2.A4

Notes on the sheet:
Current sensor 1: ISB-300-A-804
Main HV+ and HV- (Externally Fused)
Thick wires: Isolated Tractive System Thin wires: Grounded Low Voltage
See pg. 19 about Pull-Up Resistance Considerations
pin 1 and 2: HV+ Fused (1A) pin 3 and 4: IMD HV+ connector
pin 1 and 2: HV- Fused (1A) pin 3 and 4: IMD HV- connector
fclk (kHz) = 53 * 1000 / C7; C7 in pF corner frequency = fclk / 100 = 1 kHz
Split CAN termination
Capacitor used for Precharge
pin 1 and 2: HV- unfused connector pin 3 and 4: Discharge- connector
~1.60V Voltage Input Threshold corresponds to 60V on TS
Outputs ~13.2V
Current sensor 2: ISB-100-A-804

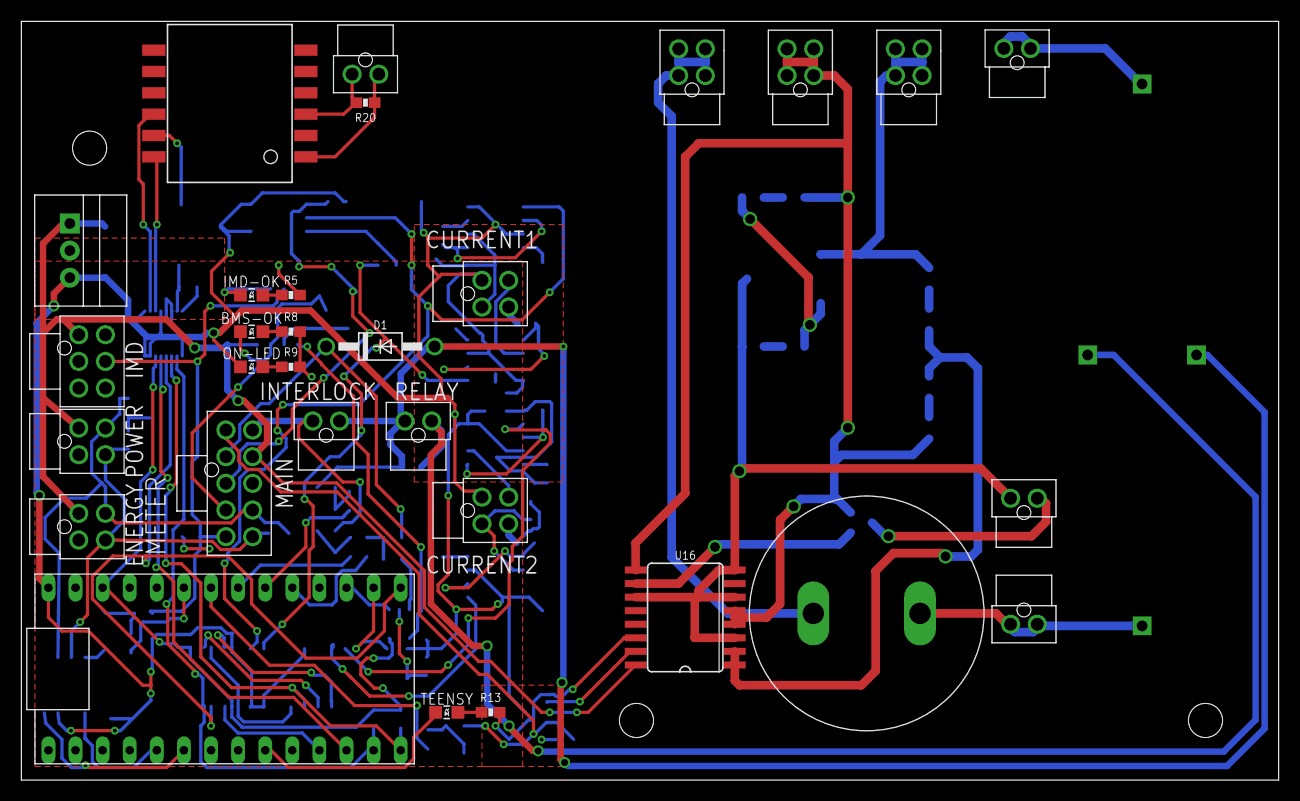
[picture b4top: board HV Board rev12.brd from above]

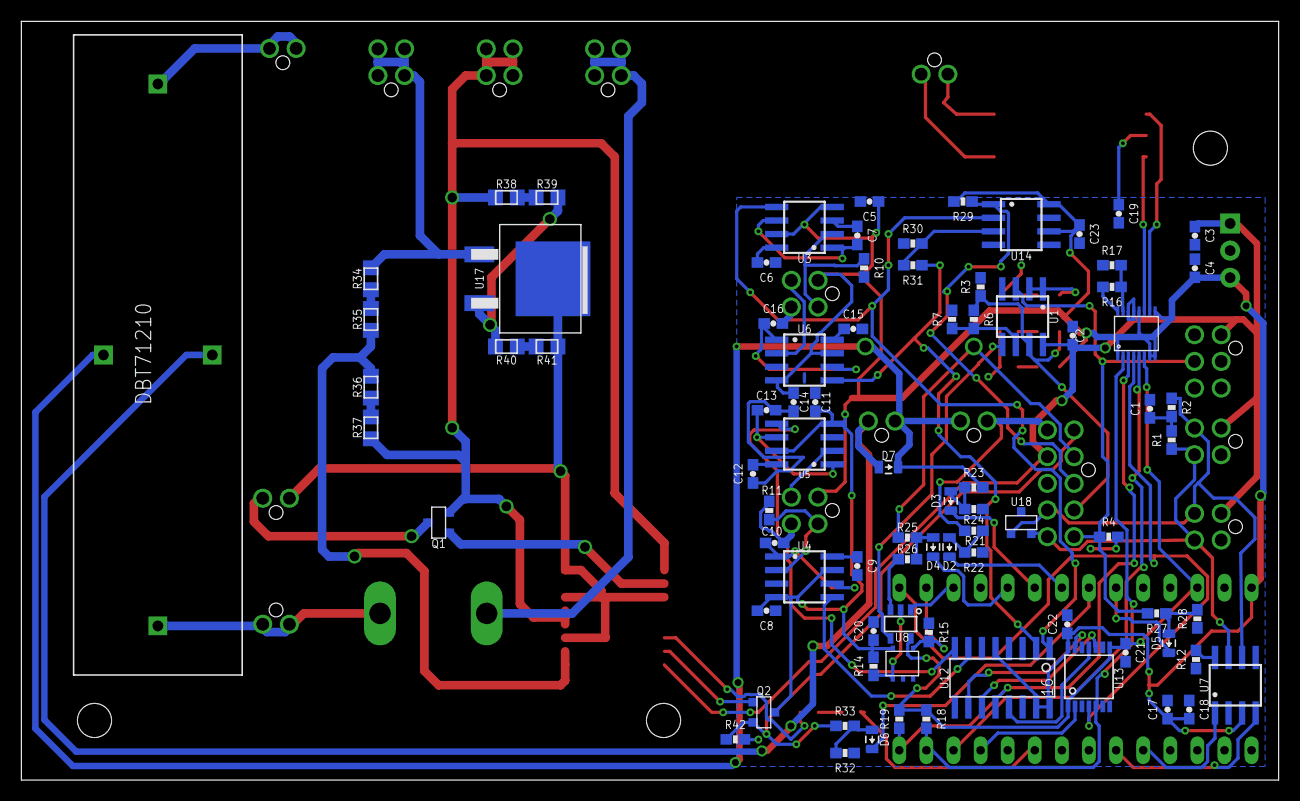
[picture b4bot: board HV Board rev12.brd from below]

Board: 2 copper layers, 117.9 x 71.1 mm, 113 parts (83 on the bottom side), 86 nets.
